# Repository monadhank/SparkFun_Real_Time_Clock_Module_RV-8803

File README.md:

SparkFun Real Time Clock RV-8803 (Qwiic)
========================================

The SparkFun Real Time Clock RV-8803 is an I<sup>2</sup>C enabled RTC module with a host of alarm, interrupt and calibration features.

Repository Contents
-------------------

* **/Documentation** - Data sheets, additional product information
* **/Hardware** - Eagle design files (.brd, .sch)
* **/Hardware/Production** - Production panel files (.brd)

Documentation
--------------
* **[SparkFun Real Time Clock RV-8803 Library](https://github.com/sparkfun/SparkFun_RV-8803_Arduino_Library)** - Arduino library for the SparkFun Real Time Clock RV-8803.
* **[SparkFun Real Time Clock RV-8803 Hookup Guide](https://learn.sparkfun.com/tutorials/sparkfun-qwiic-button-hookup-guide/all)** - Hookup Guide for the SparkFun Real Time Clock RV-8803.

Product Versions
--------------
* [BOB-16281](https://www.sparkfun.com/products/16281) - Initial release.

License Information
-------------------

This product is _**open source**_! 

Please review the LICENSE.md file for license information. 

If you have any questions or concerns on licensing, please contact technical support on our [SparkFun forums](https://forum.sparkfun.com/viewforum.php?f=152).

Distributed as-is; no warranty is given.

- Your friends at SparkFun.

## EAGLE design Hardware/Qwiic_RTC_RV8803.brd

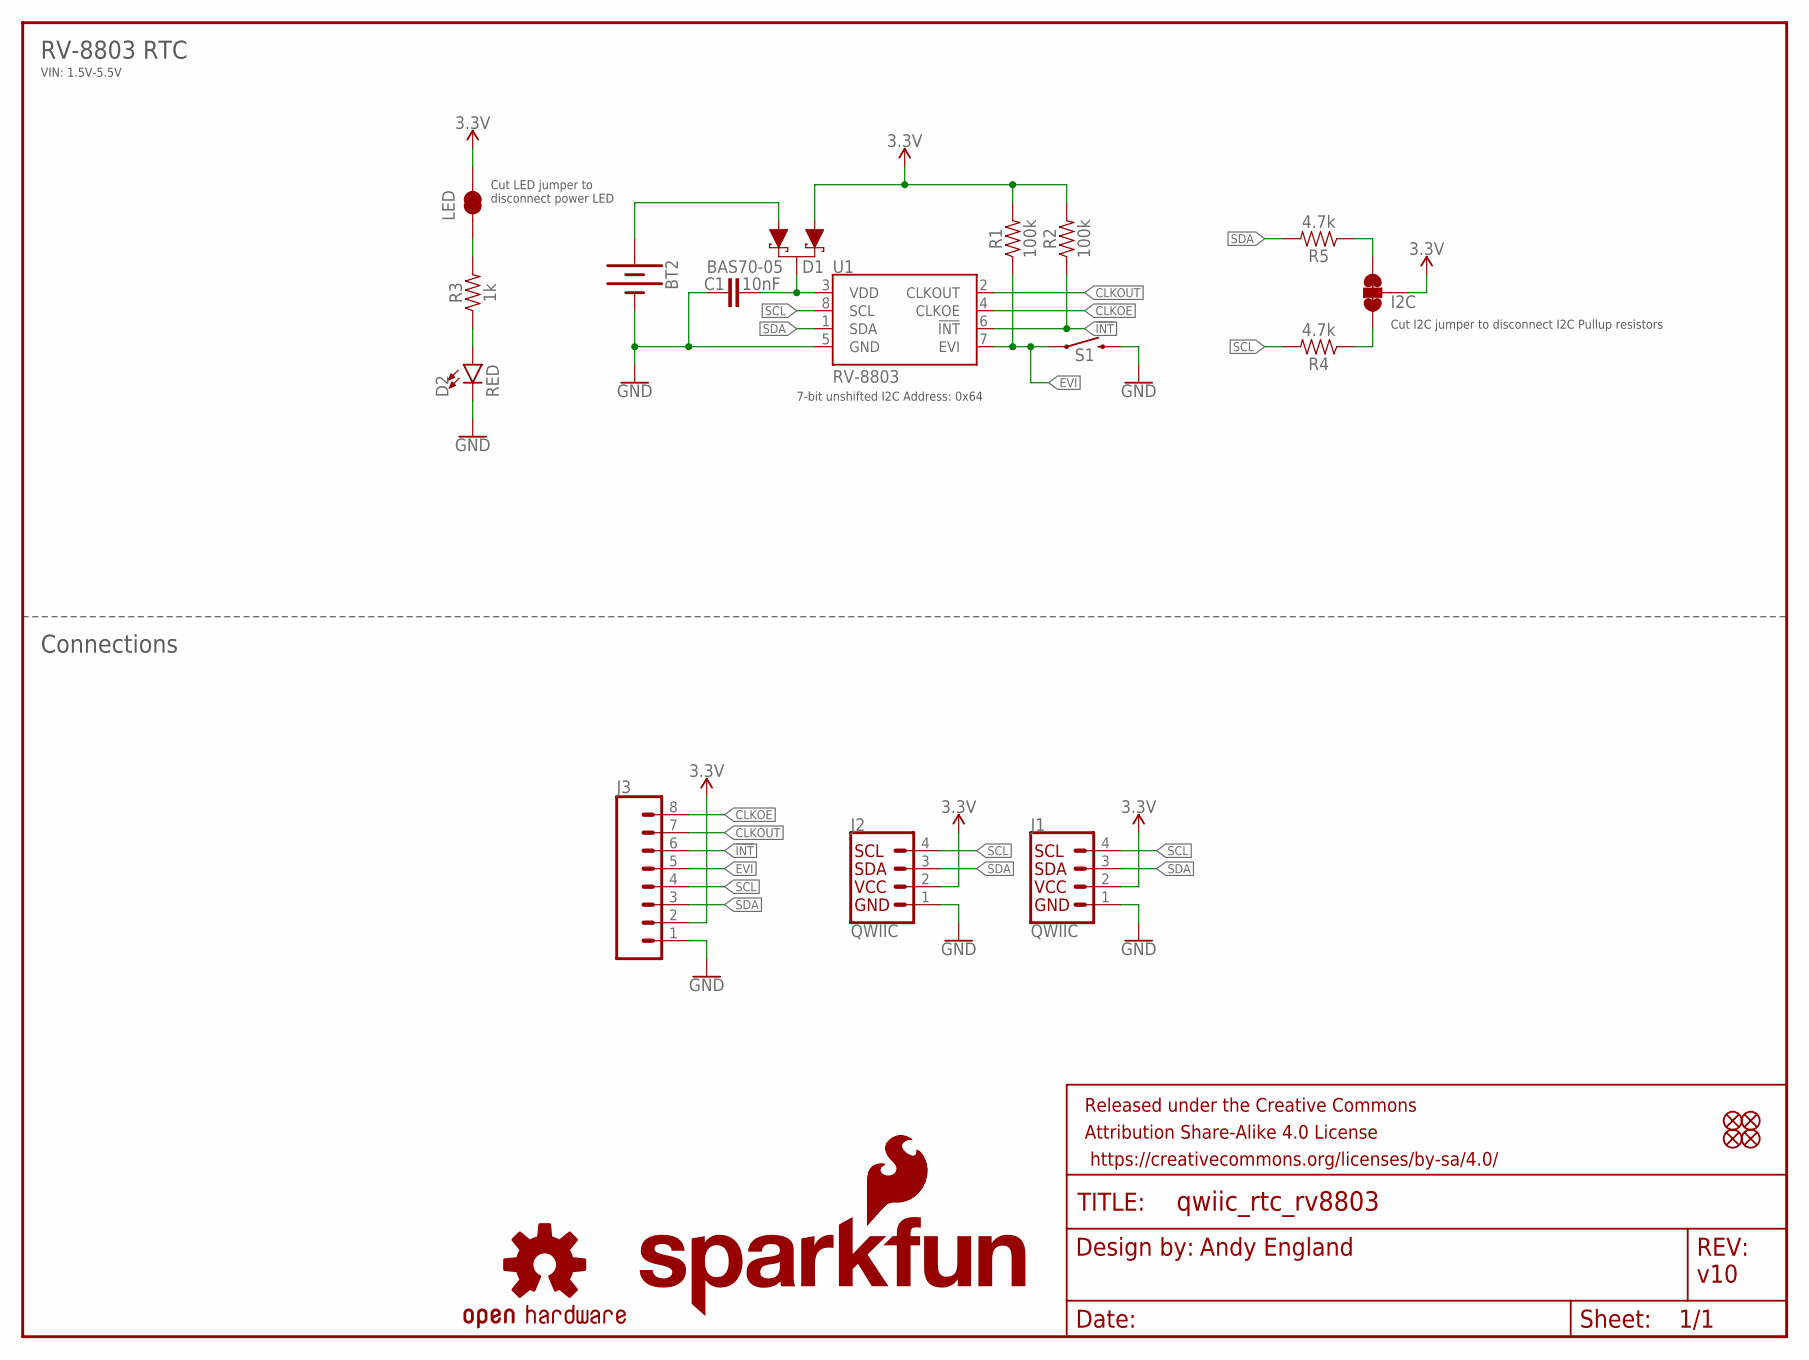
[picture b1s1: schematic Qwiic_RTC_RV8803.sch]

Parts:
BT2: BATTERY-12MM_SMD; BATTCON_12MM
C1: 10nF; 0603
D1: BAS70-05; SOT23-3
D2: RED; LED-0603
FD1, FD2, FD3, FD4: FIDUCIALUFIDUCIAL; FIDUCIAL-MICRO
FRAME1: FRAME-LETTER; CREATIVE_COMMONS
I2C: JUMPER-SMT_3_2-NC_TRACE_NO-SILK; SMT-JUMPER_3_2-NC_TRACE_NO-SILK
J1, J2: QWIIC; JST04_1MM_RA
J3: CONN_08NO_SILK_FEMALE_PTH; 1X08_NO_SILK
LED: JUMPER-SMT_2_NC_TRACE_NO-SILK; SMT-JUMPER_2_NC_TRACE_NO-SILK
LOGO1: SFE_LOGO_NAME_FLAME.1_INCH; SFE_LOGO_NAME_FLAME_.1
LOGO2: OSHW-LOGOS; OSHW-LOGO-S
LOGO3: SFE_LOGO_FLAME.1_INCH; SFE_LOGO_FLAME_.1
R1, R2: 100k; 0603
R3: 1k; 0603
R4, R5: 4.7k; 0603
S1: MOMENTARY-SWITCH-SPST-SMD-4.6X2.8MM; TACTILE_SWITCH_SMD_4.6X2.8MM
U1: RV-8803; RV-3028

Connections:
3.3V: D1.1 (A), I2C.2, J1.2, J2.2, J3.2, LED.2, R1.2, R2.2
!INT: J3.6, R2.1, U1.6 (!INT)
CLKOE: J3.8, U1.4 (CLKOE)
CLKOUT: J3.7, U1.2 (CLKOUT)
EVI: J3.5, R1.1, S1.1, S1.2 (1), U1.7 (EVI)
GND: BT2.GND (-), C1.1, D2.C, J1.1, J2.1, J3.1, S1.3 (2), S1.4 (2), U1.5 (GND)
unnamed: C1.2, D1.3 (C), U1.3 (VDD)
unnamed: D2.A, R3.1
unnamed: BT2.PWR@1 (+), D1.2 (A1)
unnamed: LED.1, R3.2
unnamed: I2C.3, R5.1
unnamed: I2C.1, R4.1
SCL: J1.4, J2.4, J3.4, R4.2, U1.8 (SCL)
SDA: J1.3, J2.3, J3.3, R5.2, U1.1 (SDA)

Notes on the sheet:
Andy England
v10
Connections
RV-8803 RTC
VIN: 1.5V-5.5V
Cut I2C jumper to disconnect I2C Pullup resistors
Cut LED jumper to disconnect power LED
7-bit unshifted I2C Address: 0x64

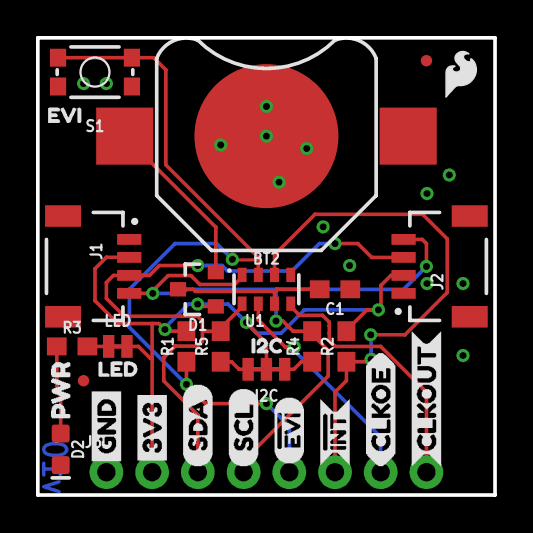
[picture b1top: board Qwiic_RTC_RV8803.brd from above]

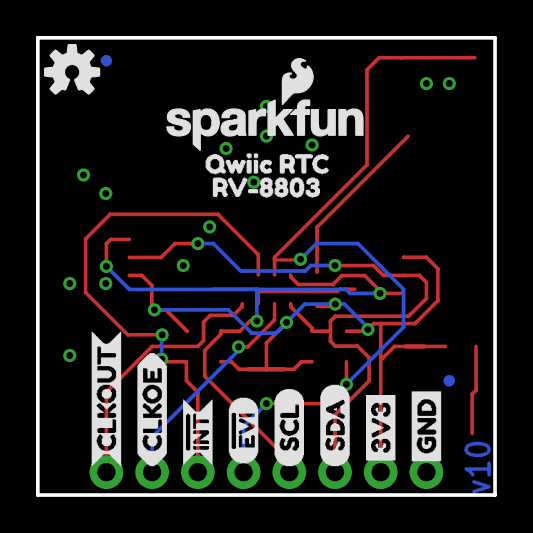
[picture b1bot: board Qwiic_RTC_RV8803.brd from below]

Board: 2 copper layers, 25.4 x 25.4 mm, 46 parts (14 on the bottom side), 14 nets.

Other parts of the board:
U$1, U$2: 3V31
U$3, U$4: GND0
U$5, U$6: SDA2
U$7, U$8: SCL3
U$9, U$10: #EVI2
U$11, U$12: CLKOUT6
U$13, U$14: CLKOE7
U$15, U$16: #INT5
U$17: PWR7
U$18: EVI1
U$19: I2C0
U$20: LED2
U$21: QWIIC_RTC0
U$22: _RV#88031

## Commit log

2020-01-28 post design review changes
2020-01-29 post checklist changes
2020-01-29 Updating silk
2020-03-02 adding resistor on OE line
2020-03-10 Create README
    Creating the initial README file.
2020-03-10 Create LICENSE.md file
2020-03-10 Cleanup and adding Documentation
    Cleaned up Hardware folder and added Application Manual for RV-8803
2020-03-25 Update Readme
    Added product photo and link to product page.

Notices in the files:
parts and their libraries:
SparkFun-Batteries: Licensing: Creative Commons ShareAlike 4.0 International - https://creativecommons.org/licenses/by-sa/4.0
SparkFun-Aesthetics: Released under the Creative Commons Attribution Share-Alike 4.0 License
SparkFun-Aesthetics: https://creativecommons.org/licenses/by-sa/4.0
